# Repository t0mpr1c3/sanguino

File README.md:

sanguino
========

Sanguino ATmega644P development board

http://sanguino.cc/hardware/

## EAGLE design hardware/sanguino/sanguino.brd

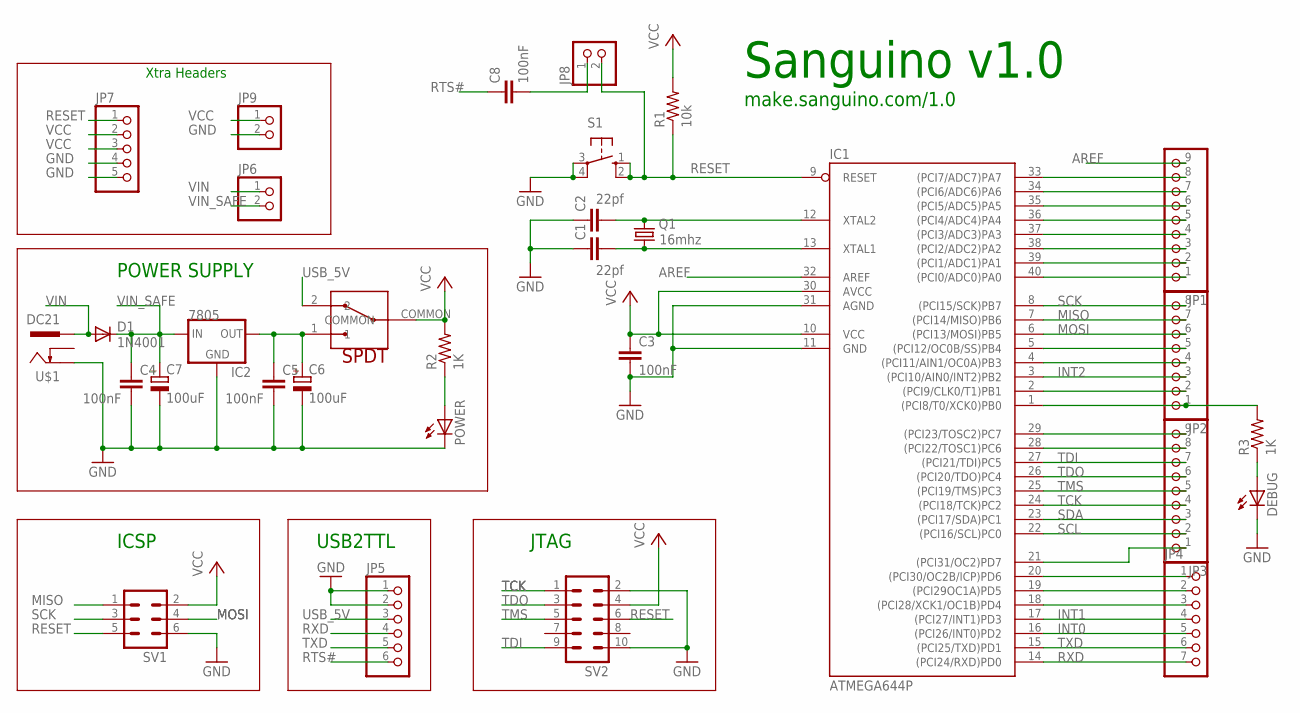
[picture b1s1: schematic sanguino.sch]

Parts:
C1, C2: 22pf; C025-025X050
C3, C4, C5, C8: 100nF; C050-030X075
C6, C7: 100uF; E2,5-6
D1: 1N4001; DO41-10
DEBUG: LED3MM
IC1: ATMEGA644P; DIL40
IC2: 7805; TO220-IGO
JP1, JP3: PINHD-1X9; 1X09
JP2: PINHD-1X8; 1X08
JP4: PINHD-1X7; 1X07
JP5: PINHD-1X6; 1X06
JP6, JP8, JP9: PINHD-1X2; 1X02
JP7: PINHD-1X5; 1X05
POWER: LED3MM
Q1: 16mhz; HC49/S
R1: 10k; 0207/7
R2, R3: 1K; 0207/2V
S1: 10-XX; B3F-10XX
SV1: ML6
SV2: ML10
U$1: DC21; DCSKT
U$2: SPDT; 10SP001

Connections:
AREF: IC1.32 (AREF), JP1.9
GND: C1.1, C2.1, C3.2, C4.2, C5.2, C6.-, C7.-, DEBUG.K (C), IC1.11 (GND), IC1.31 (AGND), IC2.GND, JP5.1, JP5.2, JP7.4, JP7.5, JP9.2, POWER.K (C), S1.3, S1.4 (P1), SV1.6, SV2.2, SV2.10, U$1.2
INT0: IC1.16 ((PCI26/INT0)PD2), JP4.5
INT1: IC1.17 ((PCI27/INT1)PD3), JP4.4
INT2: IC1.3 ((PCI10/AIN0/INT2)PB2), JP2.3
MISO: IC1.7 ((PCI14/MISO)PB6), JP2.7, SV1.1
MOSI: IC1.6 ((PCI13/MOSI)PB5), JP2.6, SV1.4
unnamed: C2.2, IC1.12 (XTAL2), Q1.2
unnamed: IC1.33 ((PCI7/ADC7)PA7), JP1.8
unnamed: IC1.34 ((PCI6/ADC6)PA6), JP1.7
unnamed: POWER.A, R2.1
unnamed: C1.2, IC1.13 (XTAL1), Q1.1
unnamed: IC1.35 ((PCI5/ADC5)PA5), JP1.6
unnamed: DEBUG.A, R3.1
unnamed: IC1.37 ((PCI3/ADC3)PA3), JP1.4
unnamed: IC1.38 ((PCI2/ADC2)PA2), JP1.3
unnamed: IC1.39 ((PCI1/ADC1)PA1), JP1.2
unnamed: IC1.40 ((PCI0/ADC0)PA0), JP1.1
unnamed: IC1.5 ((PCI12/OC0B/SS)PB4), JP2.5
unnamed: IC1.4 ((PCI11/AIN1/OC0A)PB3), JP2.4
unnamed: IC1.2 ((PCI9/CLK0/T1)PB1), JP2.2
unnamed: IC1.1 ((PCI8/T0/XCK0)PB0), JP2.1, R3.2
unnamed: IC1.29 ((PCI23/TOSC2)PC7), JP3.9
unnamed: IC1.28 ((PCI22/TOSC1)PC6), JP3.8
unnamed: IC1.21 ((PCI31/OC2)PD7), JP3.1
unnamed: IC1.36 ((PCI4/ADC4)PA4), JP1.5
unnamed: C8.2, JP8.1
unnamed: C5.1, C6.+, IC2.OUT, U$2.1
unnamed: IC1.20 ((PCI30/OC2B/ICP)PD6), JP4.1
unnamed: IC1.19 ((PCI29OC1A)PD5), JP4.2
unnamed: IC1.18 ((PCI28/XCK1/OC1B)PD4), JP4.3
RESET: IC1.9 (RESET), JP7.1, JP8.2, R1.1, S1.1 (S), S1.2 (S1), SV1.5, SV2.6
RTS#: C8.1, JP5.6
RXD: IC1.14 ((PCI24/RXD)PD0), JP4.7, JP5.4
SCK: IC1.8 ((PCI15/SCK)PB7), JP2.8, SV1.3
SCL: IC1.22 ((PCI16/SCL)PC0), JP3.2
SDA: IC1.23 ((PCI17/SDA)PC1), JP3.3
TCK: IC1.24 ((PCI18/TCK)PC2), JP3.4, SV2.1
TDI: IC1.27 ((PCI21/TDI)PC5), JP3.7, SV2.9
TDO: IC1.26 ((PCI20/TDO)PC4), JP3.6, SV2.3
TMS: IC1.25 ((PCI19/TMS)PC3), JP3.5, SV2.5
TXD: IC1.15 ((PCI25/TXD)PD1), JP4.6, JP5.5
USB_5V: JP5.3, U$2.2
VCC: C3.1, IC1.10 (VCC), IC1.30 (AVCC), JP7.2, JP7.3, JP9.1, R1.2, R2.2, SV1.2, SV2.4, U$2.COMMON
VIN: D1.A, JP6.1, U$1.1
VIN_SAFE: C4.1, C7.+, D1.C, IC2.IN, JP6.2

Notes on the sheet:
ICSP
USB2TTL
POWER SUPPLY
Sanguino v1.0
make.sanguino.com/1.0
JTAG
Xtra Headers

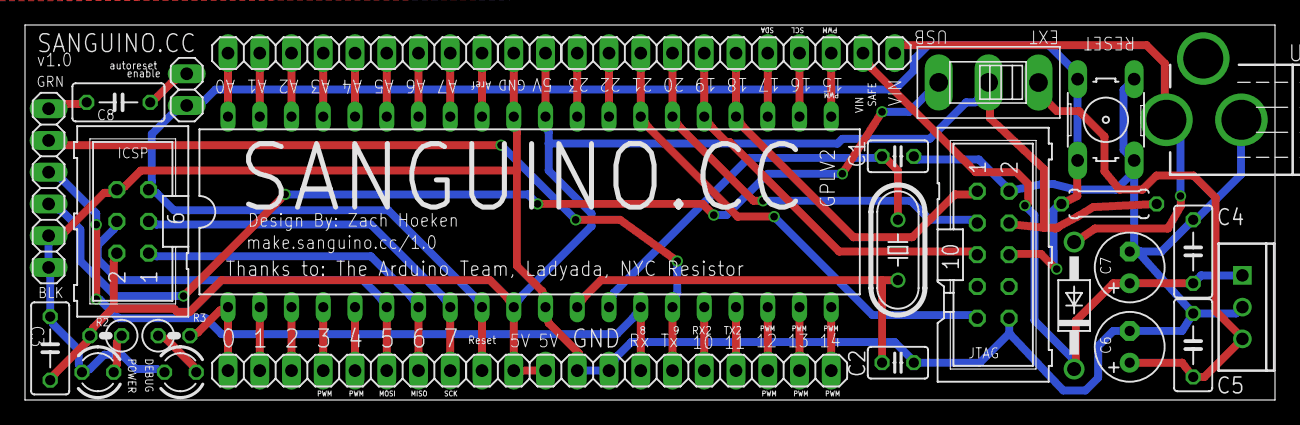
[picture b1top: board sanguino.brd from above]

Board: 4 copper layers, 100.0 x 30.0 mm, 31 parts (0 on the bottom side), 46 nets.

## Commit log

2013-11-25 3x Sanguino panelized in 10cm x 10cm PCB
2013-11-25 original hardware files
2013-12-03 sanguino_3x for Seeedstudio
2013-12-04 sanguino_3x Elecrow order

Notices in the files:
hardware/sanguino/sanguino.brd:
GPLV2
